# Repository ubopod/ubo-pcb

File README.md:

# Ubo PCBs

Open hardware design files for the printed circuit boards in the [Ubo Pod](https://getubo.com)
and its accessories — the main Raspberry Pi HAT, the side connector board, PCIe and M.2
adapters, a flex cable, and an NFC board. Sources are a mix of **Eagle CAD** and **KiCad**;
newer designs are KiCad.

<table>
  <tr>
    <td align="center" width="33%">
      <br>
      <sub><b><a href="boards/ubo-sideboard/">Sideboard</a></b><br>ports to the back panel</sub>
    </td>
    <td align="center" width="33%">
      <br>
      <sub><b><a href="boards/ubo-hab-v2/">HAB v2</a></b><br>PCIe, USB-C PD and PoE+</sub>
    </td>
    <td align="center" width="33%">
      <br>
      <sub><b><a href="boards/ubo-pcie-adapter/">PCIe adapter</a></b><br>M.2 M-key for the Pi 5</sub>
    </td>
  </tr>
  <tr>
    <td align="center">
      <br>
      <sub><b><a href="boards/m2-mkey-to-aekey/">M.2 M-key to A/E-key</a></b><br>runs a Google Coral</sub>
    </td>
    <td align="center">
      <br>
      <sub><b><a href="boards/pcie-fpc-s-shaped/">S-shaped PCIe FPC</a></b><br>2-layer flex cable</sub>
    </td>
    <td align="center">
      <br>
      <sub><b>As fabricated</b><br>a populated sideboard</sub>
    </td>
  </tr>
</table>

## Boards

Each board lives in its own directory under [`boards/`](boards/) with its own README.

| Board | Rev | Tool | Status | Connects to |
|---|---|---|---|---|
| [**ubo-top-hat**](boards/ubo-top-hat/) | v1.6 | Eagle | Production | Raspberry Pi 40-pin header |
| [**ubo-sideboard**](boards/ubo-sideboard/) | v1.5.2 | KiCad | Current | Pi 4/5 side ports + top HAT |
| ↳ [v1.4](boards/ubo-sideboard/v1.4-eagle/) | v1.4 | Eagle | Superseded by v1.5.2 | — |
| [**ubo-hab-v2**](boards/ubo-hab-v2/) | v4 | KiCad | Current | Raspberry Pi 5 PCIe + power |
| [**ubo-pcie-adapter**](boards/ubo-pcie-adapter/) | v3 | KiCad | Superseded by HAB v2 | Raspberry Pi 5 PCIe |
| [**m2-mkey-to-aekey**](boards/m2-mkey-to-aekey/) | — | KiCad | Built and tested | M.2 M-key slot |
| [**pcie-fpc-s-shaped**](boards/pcie-fpc-s-shaped/) | v2 | KiCad | Prototype, revision in progress | PCIe adapter FPC connectors |
| [**ubo-nfc-hat**](boards/ubo-nfc-hat/) | 1.0 | KiCad | Experimental | I²C via 1×8 headers |

**What each one is:**

- **ubo-top-hat** — the main Ubo board. LCD, keypad, RGB LED ring, WM8960 audio with speakers and
  microphones, IR transmit/receive, temperature and light sensors, EEPROM, fan, power button, and
  an experimental SDR section.
- **ubo-sideboard** — brings the Pi's mini HDMI, USB-C power, and audio jack around to the back of
  the enclosure, and adds a microSD extender, STEMMA Qt connectors, a power button, and a fan header.
- **ubo-hab-v2** — "hardware added on the bottom." PCIe to M.2 M-key, with optional USB-C PD and
  PoE+ power input modules and 12V/5V/3.3V breakouts.
- **ubo-pcie-adapter** — the first HAB revision; a simpler PCIe to M.2 M-key adapter.
- **m2-mkey-to-aekey** — adapts an M.2 M-key slot to A/E-key, so a Google Coral accelerator can go
  where an NVMe drive would.
- **pcie-fpc-s-shaped** — a 2-layer S-shaped FPC cable matching the connector positions on the
  PCIe adapter.
- **ubo-nfc-hat** — NTAG I²C plus NFC tag with a chain of addressable RGB LEDs.

## Repository layout

One directory per board. Within a board directory:

```
boards/<board>/
  README.md          documentation for this board
  <design files>     KiCad project or Eagle .sch/.brd at the top level,
                     or in a <rev>-<tool>/ subdirectory when a board has
                     more than one revision (see ubo-sideboard)
  images/            renders, layout screenshots, photos
  docs/              exported schematic and assembly PDFs
  datasheets/        datasheets for the components used on this board
  mechanical/        board outline DXF, STEP and other 3D models
```

Not every board has every subdirectory — they exist where there is something to put in them.

## Opening the files

- **KiCad projects** (`.kicad_pro`) — KiCad 8 or 9. Open the `.kicad_pro`, not the individual
  schematic or board files, so the project's library tables load.
- **Eagle designs** (`.sch` / `.brd`) — authored in Eagle CAD 9.6.2. KiCad can also import them
  via *File → Import → Non-KiCad Project*.

## License

Copyright © Ubo Pod.

These designs are licensed under the **CERN Open Hardware Licence Version 2 – Strongly
Reciprocal** (`CERN-OHL-S-2.0`). The full text is in [LICENSE](LICENSE).

In plain terms:

- **You can** use, study, modify, manufacture, and sell these boards, commercially or not.
- **If you distribute a modified design**, you have to release your modified source under this
  same licence, so the next person gets what you got.
- **If you sell or give away a product** made from these designs, you have to tell the recipient
  where to obtain the source for it.
- **There is no warranty.** These are hobbyist and small-batch designs; verify them yourself
  before committing to a fabrication run.

That summary is for orientation only — [LICENSE](LICENSE) is the document that actually governs.

To reuse a board here, keep the copyright and licence notices in the design files, and note your
own changes.

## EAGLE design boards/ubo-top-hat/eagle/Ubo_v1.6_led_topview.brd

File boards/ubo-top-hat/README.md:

# Ubo Top HAT (Top PCB)

The main Ubo board — a Raspberry Pi HAT carrying the display, keypad, LED ring, audio, sensors, and IR.
Designed in Eagle CAD 9.6.2. See the [repository index](../../README.md) for the other boards.

| | |
|---|---|
| **Revision** | v1.6 (Eagle source) / v1.6.1 (exported schematic PDF) |
| **Tool** | Eagle CAD 9.6.2 |
| **Interface** | Raspberry Pi 40-pin header |

## Files

| Path | Contents |
|---|---|
| [`eagle/`](eagle/) | Eagle schematic and board layout (`Ubo_v1.6_led_topview.sch` / `.brd`) |
| [`docs/`](docs/) | [Full SKU schematic PDF (v1.6.1)](docs/Ubo_v1.6.1_schematic_full_SKU.pdf) |
| [`datasheets/`](datasheets/) | Datasheets for the components used below |
| [`images/`](images/) | Schematic excerpts for each sub-system |
| [`mechanical/`](mechanical/) | Board outline DXF and 3D model archive |

## Top PCB Overview

In designing Ubo Top PCB (HAT), we tried to use popular components that have already gained adoption among the developer community and are developer friendly. In addition, we made sure that we can source these components for manufacturing. There are several development boards with one or several of these components that you can buy from either Sparkfun, Adafruit, Tindie, SeedStudio or other vendors. At the end of this repo, we have provided links to some of the development boards as reference.

The main objective in designing Ubo was centred around improving developer and end-user experience through offering a rich user interface. Since Raspberry Pi by itself is just a compute brain with no peripherals, it is often challenging to offer a compelling UX/UI to the end user without an interface.

In the following section, we discuss how each sub-system was chosen to enhance user and developer experience as well as technical details of implementation.

## RASPBERRY PI HEADER

## LCD

backlight is connected to GPIO26
TODO: link to datasheet

## Keypad

You can access the datasheet for GPIO Expander [here](datasheets/AW9523_GPIO_expander.pdf)

## RGB LED Ring

## Audio
### Speakers
### Line Out
### Microphones

## Temperature sensor

## Light Sensor

## EEPROM

## Fan

## Power Button

## Security

## Experimental SDR

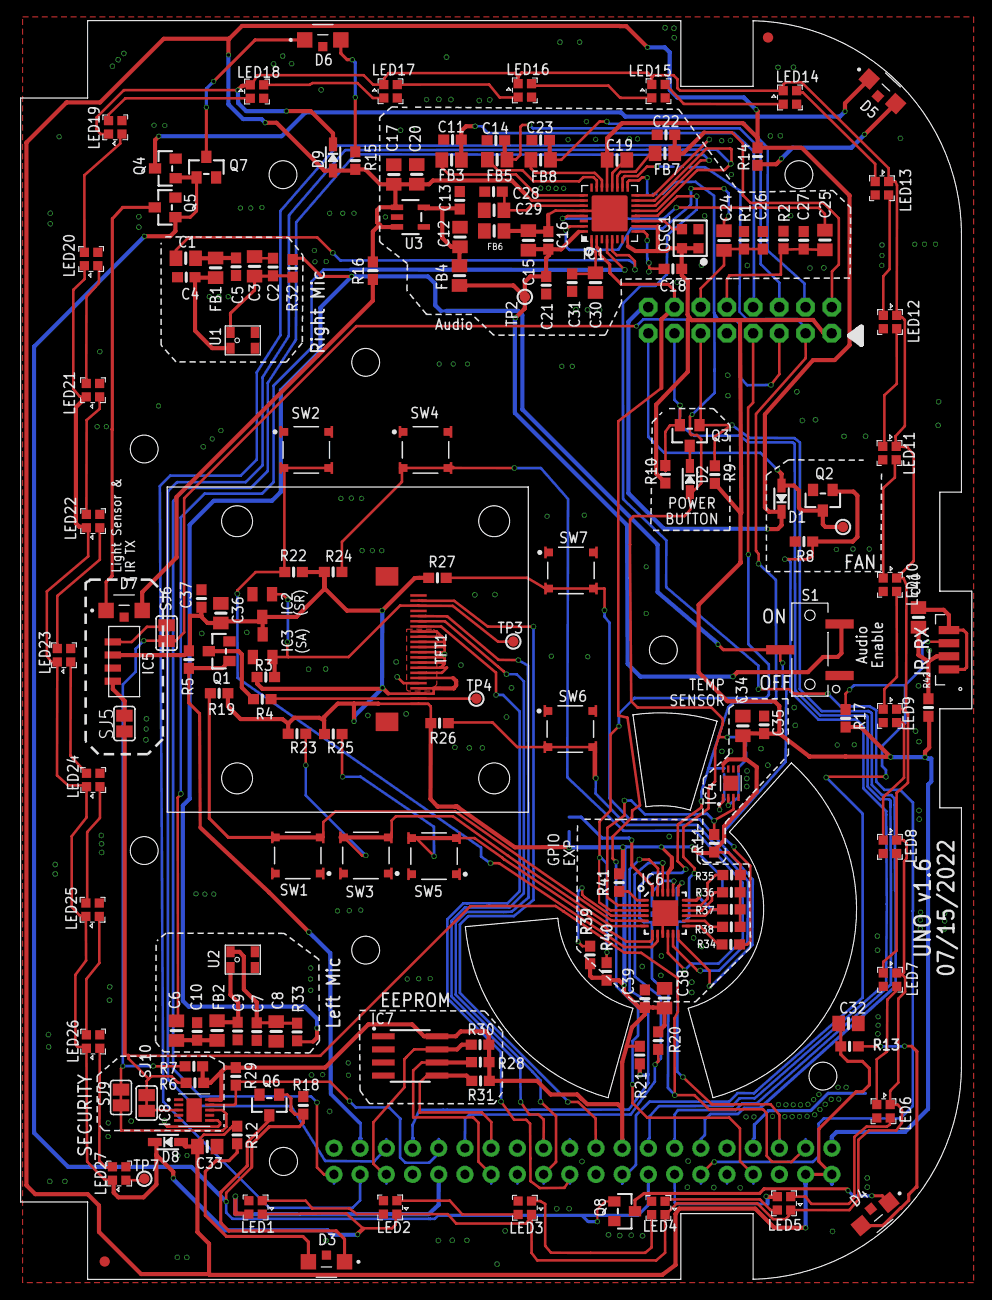
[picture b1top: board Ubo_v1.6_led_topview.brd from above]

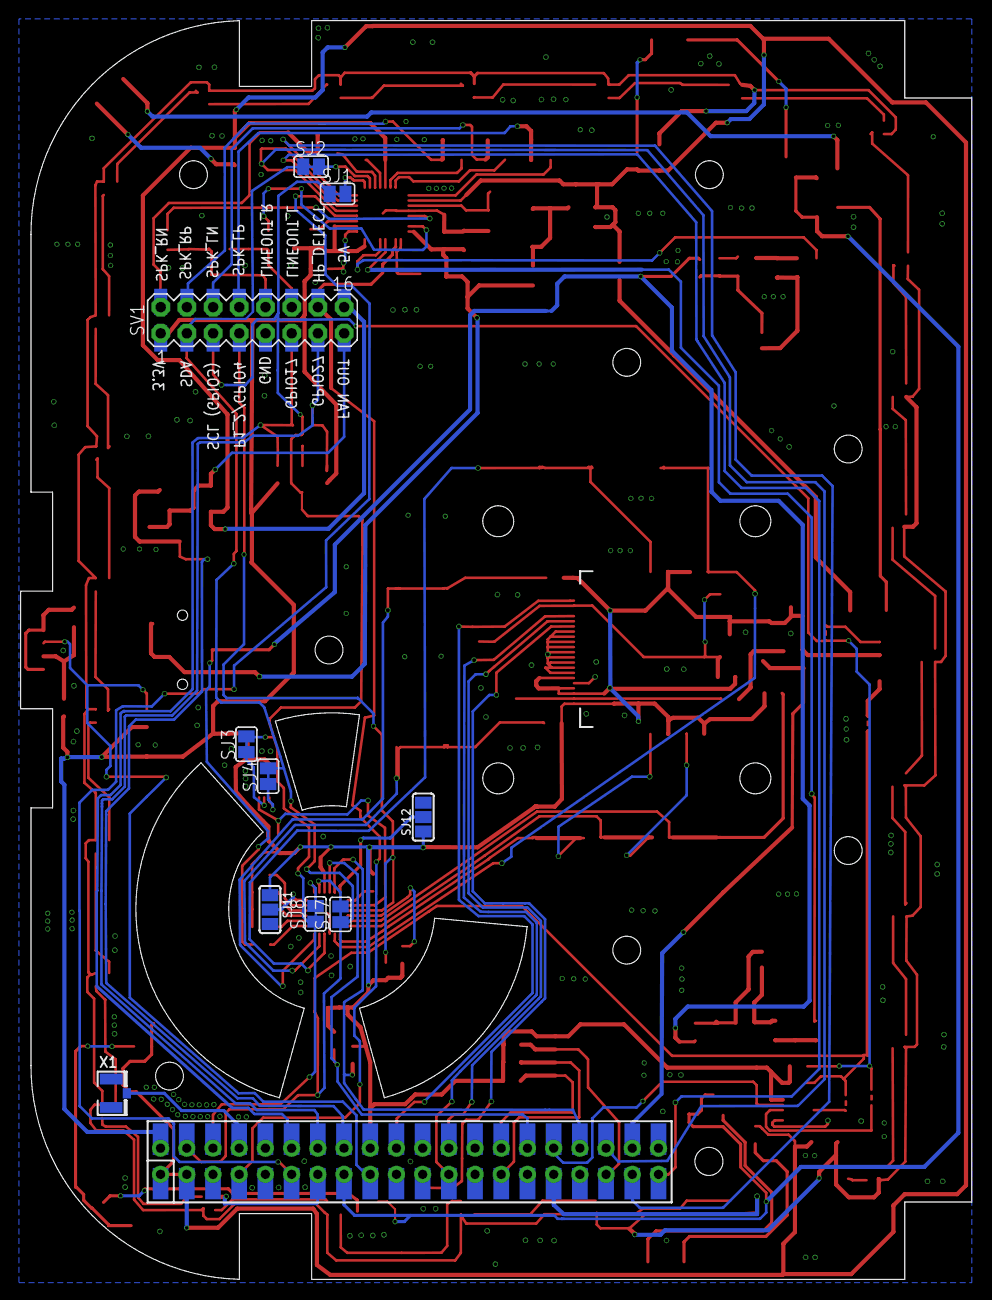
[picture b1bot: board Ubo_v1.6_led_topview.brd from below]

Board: 2 copper layers, 92.2 x 122.0 mm, 178 parts (10 on the bottom side), 130 nets.

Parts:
C1, C3, C6, C8, C12, C15, C17, C19, C20, C29, C30, C32, C33, C34, C36, C38, C40: 10uF; 0805-NO
C2, C7, C13, C16, C18, C21, C28, C31, C35, C37, C39: 0.1uF; 0603-NO
C4, C5, C9, C10: 33pF; 0603-NO
C11, C14, C22, C23, C26, C27: 100pF; 0603-NO
C24, C25: 47uF; 0805-NO
D1, D2, D8, D9: 1N4148; SOD-323
D3, D4, D5, D6, D7: VSMB10940; DIO_VSMB10940
FB1, FB2, FB3, FB4, FB5, FB6, FB7, FB8: Ferrite; 0805-NO
FID1, FID2: FIDUCIAL_1MM
IC1: WM8960; QFN32_5MM
IC2, IC3: APX803-SAG; SOT23
IC4: PCT2075D8-HWSON; SON127P600X800X80-9N
IC5: VEML7700
IC6: AW9523; QFN24_4MM_SMSC
IC7: CAT24C32WI-GT3; SOIC127P600X175-8N
IC8: SLS32AIA020X2USON10XTMA4; SON50P300X300X60-11N
IR1: TSMP77000
LED1, LED2, LED3, LED4, LED5, LED6, LED7, LED8, LED9, LED10, LED11, LED12, LED13, LED14, LED15, LED16, LED17, LED18, LED19, LED20, LED21, LED22, LED23, LED24, LED25, LED26, LED27: LC8812B-3210; SK6805-EC15
OSC1: ECS-3225MV; OSC_2.5X2MM
Q1, Q2, Q3, Q4, Q5, Q6, Q7, Q8: BSS138; SOT23-WIDE
R1, R2, R3, R5, R6, R7, R8, R9, R10, R11, R17, R18, R19, R20, R21, R22, R23, R24, R25, R26, R27, R29, R30, R34, R35, R36, R37, R38, R39, R40, R41: 10K; 0603-NO
R4, R12, R13, R14, R15, R16, R32, R33, R42: 20; 0603-NO
R28, R31: 3.9K; 0603-NO
RPI1: RASPBERRYPI_BPLUS_PIN_2X20_SMTTHM; PI_PIN_2X20_SMTTHM
S1: JS102011JCQNMS-12D17E; SW_MS-12D17E
SJ1, SJ2, SJ3, SJ4, SJ5, SJ6, SJ7, SJ8, SJ9, SJ10: SJ
SJ11, SJ12: SOLDERJUMPER_2WAY_OPEN_NOPASTE
SV1: MA08-2
SW1, SW2, SW3, SW4, SW5, SW6, SW7: E-SWITCH_TL3315NF160Q_0
TFT1: DISP_TFT_1.54IN_240X240_22P_TOP_FPC; TFT_1.54IN_240X240_22PN_TOP_FPC
TP2, TP3, TP4, TP6, TP7: TESTPOINT_ROUND_1MM
U1, U2: MIC; SPW2430HR5H-B
U3: AP2112-3.3K; SOT23-5
X1: U.FL

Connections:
3.3V: C18.1, C34.1, C35.1, C36.1, C37.1, C38.1, C39.1, IC1.8, IC1.10, IC2.3, IC3.3, IC4.P$8, IC5.2, IC6.21, IC7.8, IC8.10, OSC1.1, OSC1.4, R3.2, R5.2, R6.1, R7.1, R9.1, R10.1, R11.1, R17.1, R19.1, R20.1, R21.1, R22.1, R23.1, R24.1, R25.1, R26.1, R27.1, R28.1, R29.1, R30.1, R31.1, R35.1, R36.1, R37.1, R38.1, R39.1, R40.1, R41.1, R42.1, RPI1.1, RPI1.17, RPI1.S1, RPI1.S17, SJ11.1, SJ12.1, SV1.1, SV1.P$1, TFT1.1, TFT1.3, TFT1.4, TFT1.6
5.0V: C17.1, C19.1, C20.1, C32.1, C33.1, D1.C, D8.A, D9.A, IC1.21, IC1.26, R12.1, R13.1, R14.1, R15.1, R16.1, RPI1.2, RPI1.4, RPI1.S2, RPI1.S4, SV1.16, SV1.P$16, U3.1, U3.3
AGND: C15.2, C16.2, FB6.1, IC1.28, IC1.33
AVDD: C15.1, C16.1, C21.1, FB4.1, IC1.32, S1.3, TP2.P$1
AVDD_EN: R32.2, R33.2, R34.2, S1.2
BUTTON_E_DOWN: IC6.10, R24.2, SW4.3, SW4.3-2, SW4.4, SW4.4-2
BUTTON_E_UP: IC6.8, R22.2, SW2.3, SW2.3-2, SW2.4, SW2.4-2
BUTTON_S_LEFT: IC6.11, R26.2, SW6.3, SW6.3-2, SW6.4, SW6.4-2
BUTTON_S_RIGHT: IC6.12, R27.2, SW7.3, SW7.3-2, SW7.4, SW7.4-2
BUTTON_W_DOWN: IC6.7, R25.2, SW5.3, SW5.3-2, SW5.4, SW5.4-2
BUTTON_W_MIDDLE: IC6.6, R23.2, SW3.3, SW3.3-2, SW3.4, SW3.4-2
BUTTON_W_UP: IC6.5, R19.2, SW1.3, SW1.3-2, SW1.4, SW1.4-2
EECLK: IC7.6, R28.2, RPI1.28, RPI1.S28
EEDATA: IC7.5, R31.2, RPI1.27, RPI1.S27
EEPROM_WP: IC7.7, R30.2, RPI1.36, RPI1.S36
FAN_IN: Q2.1, R8.1, RPI1.15, RPI1.S15
FAN_OUT: D1.A, Q2.3, SV1.15, SV1.P$15, TP6.P$1
GND: C2.2, C3.2, C4.2, C5.2, C7.2, C8.2, C9.2, C10.2, C11.2, C12.2, C13.2, C14.2, C17.2, C18.2, C19.2, C20.2, C21.2, C22.2, C23.2, C26.2, C27.2, C28.2, C29.2, C30.2, C31.2, C32.2, C33.2, C34.2, C35.2, C36.2, C37.2, C38.2, C39.2, C40.2, FB6.2, IC1.9, IC1.20, IC1.24, IC2.2, IC3.1, IC4.P$4, IC4.P$5, IC4.P$6, IC4.P$7, IC4.P$9, IC5.3, IC6.9, IC6.THERM, IC7.1, IC7.2, IC7.3, IC7.4, IC8.1, IC8.2, IC8.4, IC8.5, IC8.6, IC8.7, IC8.11, IR1.P$1, IR1.P$4, LED1.P$4, LED2.P$4, LED3.P$4, LED4.P$4, LED5.P$4, LED6.P$4, LED7.P$4, LED8.P$4, LED9.P$4, LED10.P$4, LED11.P$4, LED12.P$4, LED13.P$4, LED14.P$4, LED15.P$4, LED16.P$4, LED17.P$4, LED18.P$4, LED19.P$4, LED20.P$4, LED21.P$4, LED22.P$4, LED23.P$4, LED24.P$4, LED25.P$4, LED26.P$4, LED27.P$4, OSC1.2, Q1.2, Q2.2, Q4.2, Q5.2, Q6.2, Q7.2, Q8.2, R1.1, R2.1, R8.2, R18.2, RPI1.6, RPI1.9, RPI1.14, RPI1.20, RPI1.25, RPI1.30, RPI1.34, RPI1.39, RPI1.S6, RPI1.S9, RPI1.S14, RPI1.S20, RPI1.S25, RPI1.S30, RPI1.S34, RPI1.S39, S1.1, SJ11.3, SJ12.3, SV1.9, SV1.P$9, SW1.1, SW1.1-2, SW1.2, SW1.2-2, SW2.1, SW2.1-2, SW2.2, SW2.2-2, SW3.1, SW3.1-2, SW3.2, SW3.2-2, SW4.1, SW4.1-2, SW4.2, SW4.2-2, SW5.1, SW5.1-2, SW5.2, SW5.2-2, SW6.1, SW6.1-2, SW6.2, SW6.2-2, SW7.1, SW7.1-2, SW7.2, SW7.2-2, TFT1.5, TFT1.7, TFT1.8, TFT1.9, TFT1.10, TFT1.11, TFT1.12, TFT1.13, TFT1.14, TFT1.15, TFT1.22, TFT1.SUPPORT1, TFT1.SUPPORT2, U1.2, U1.3, U2.2, U2.3, U3.2, X1.1, X1.2
GPIO4: RPI1.7, RPI1.S7, X1.3
GPIO17: Q3.1, R9.2, RPI1.11, RPI1.S11, SV1.11, SV1.P$11
GPIO27: Q3.2, R10.2, RPI1.13, RPI1.S13, SV1.13, SV1.P$13
GPIO_15: RPI1.10, RPI1.S10
GPIO_EXP_RST: IC6.23, R21.2, RPI1.33, RPI1.S33
HEADPHONE_DETECT: IC1.2, RPI1.8, RPI1.S8, SV1.14, SV1.P$14
I2S_BCLK: IC1.12, RPI1.12, RPI1.S12
I2S_DIN: IC1.16, RPI1.38, RPI1.S38
I2S_DOUT: IC1.14, RPI1.40, RPI1.S40
I2S_LRCLK: IC1.13, IC1.15, RPI1.35, RPI1.S35
INT: IC6.22, R20.2, RPI1.29, RPI1.S29
IR_RX: IR1.P$3, R17.2, RPI1.18, RPI1.S18
IR_TX: Q4.1, Q5.1, Q6.1, Q7.1, Q8.1, R18.1, RPI1.16, RPI1.S16
LEDK: R4.2, TFT1.2, TP4.P$1
LED_POWER: D8.C, D9.C, LED1.P$2, LED2.P$2, LED3.P$2, LED4.P$2, LED5.P$2, LED6.P$2, LED7.P$2, LED8.P$2, LED9.P$2, LED10.P$2, LED11.P$2, LED12.P$2, LED13.P$2, LED14.P$2, LED15.P$2, LED16.P$2, LED17.P$2, LED18.P$2, LED19.P$2, LED20.P$2, LED21.P$2, LED22.P$2, LED23.P$2, LED24.P$2, LED25.P$2, LED26.P$2, LED27.P$2
LED_PWM0: LED1.P$1, RPI1.32, RPI1.S32
LINEOUT_LEFT: C24.2, C26.1, R1.2, SV1.12, SV1.P$12
LINEOUT_RIGHT: C25.2, C27.1, R2.2, SV1.10, SV1.P$10
LINPUT1: C6.2, IC1.4
LITE: Q1.1, R5.1, RPI1.37, RPI1.S37
MCLK: IC1.11, OSC1.3
MICBIAS: C30.1, C31.1, IC1.1
unnamed: FB7.1, IC1.19
unnamed: FB8.1, IC1.22
unnamed: LED27.P$3, TP7.P$1
unnamed: Q1.3, R4.1
unnamed: IC6.20, SJ7.2
unnamed: D7.A, R16.2
unnamed: D3.C, Q6.3
unnamed: D2.C, Q3.3
unnamed: IC6.19, SJ8.2
unnamed: IC6.4, R39.2
unnamed: IC6.14, R38.2
unnamed: C4.1, FB1.1, U1.1
unnamed: C9.1, FB2.1, U2.1
unnamed: LED1.P$3, LED2.P$1
unnamed: LED2.P$3, LED3.P$1
unnamed: C1.1, C5.1, FB1.2
unnamed: C6.1, C10.1, FB2.2
unnamed: LED3.P$3, LED4.P$1
unnamed: IC6.15, R37.2
unnamed: LED4.P$3, LED5.P$1
unnamed: FB3.1, IC1.25
unnamed: FB5.1, IC1.23
unnamed: LED6.P$3, LED7.P$1
unnamed: LED7.P$3, LED8.P$1
unnamed: LED9.P$3, LED10.P$1
unnamed: LED10.P$3, LED11.P$1
unnamed: LED14.P$3, LED15.P$1
unnamed: LED15.P$3, LED16.P$1
unnamed: LED16.P$3, LED17.P$1
unnamed: LED17.P$3, LED18.P$1
unnamed: LED20.P$3, LED21.P$1
unnamed: LED21.P$3, LED22.P$1
unnamed: LED22.P$3, LED23.P$1
unnamed: LED23.P$3, LED24.P$1
unnamed: LED5.P$3, LED6.P$1
unnamed: LED13.P$3, LED14.P$1
unnamed: LED19.P$3, LED20.P$1
unnamed: IC6.16, R36.2
unnamed: LED11.P$3, LED12.P$1
unnamed: LED12.P$3, LED13.P$1
unnamed: LED24.P$3, LED25.P$1
unnamed: LED25.P$3, LED26.P$1
unnamed: C24.1, IC1.31
unnamed: C25.1, IC1.29
unnamed: IC6.17, R35.2
unnamed: IC1.17, SJ1.2
unnamed: IC1.18, SJ2.2
unnamed: IC5.4, SJ5.2
unnamed: IC5.1, SJ6.2
unnamed: IC4.P$2, SJ3.1
unnamed: IC4.P$1, SJ4.1
unnamed: IC8.8, SJ9.2
unnamed: IC8.3, SJ10.2
unnamed: D6.A, R15.2
unnamed: D5.A, R14.2
unnamed: D4.A, R13.2
unnamed: D3.A, R12.2
unnamed: LED8.P$3, LED9.P$1
unnamed: LED18.P$3, LED19.P$1
unnamed: LED26.P$3, LED27.P$1
unnamed: C7.1, C8.1, R33.1, U2.4
unnamed: C2.1, C3.1, R32.1, U1.4
unnamed: IC6.13, R34.1
unnamed: IC6.24, SJ12.2
unnamed: IC6.18, SJ11.2
unnamed: D5.C, Q4.3
unnamed: D4.C, Q8.3
unnamed: D6.C, Q7.3
unnamed: D7.C, Q5.3
unnamed: C40.1, IR1.P$2, R42.2
OUT: C12.1, C13.1, FB4.2, U3.5
P1_0: IC6.1, R41.2
P1_2: IC6.3, R40.2, SV1.7, SV1.P$7
RINPUT1: C1.2, IC1.5
SCL: D2.A, R7.2, RPI1.5, RPI1.S5, SJ1.1, SJ3.2, SJ6.1, SJ8.1, SJ9.1, SV1.5, SV1.P$5
SDA: R6.2, RPI1.3, RPI1.S3, SJ2.1, SJ4.2, SJ5.1, SJ7.1, SJ10.1, SV1.3, SV1.P$3
SECURITY_RESET: IC8.9, R29.2, RPI1.31, RPI1.S31
SPI_CE1: RPI1.26, RPI1.S26
SPI_MISO: RPI1.21, RPI1.S21
SPK_LN: C14.1, FB5.2, SV1.6, SV1.P$6
SPK_LP: C11.1, FB3.2, SV1.8, SV1.P$8
SPK_RN: C22.1, FB7.2, SV1.2, SV1.P$2
SPK_RP: C23.1, FB8.2, SV1.4, SV1.P$4
TEMP_INT: IC4.P$3, IC6.2, R11.2
TFT_CS: RPI1.24, RPI1.S24, TFT1.18
TFT_DC: RPI1.22, RPI1.S22, TFT1.16
TFT_MOSI: RPI1.19, RPI1.S19, TFT1.21
TFT_RESET: IC2.1, IC3.2, R3.1, TFT1.20, TP3.P$1
TFT_SCLK: RPI1.23, RPI1.S23, TFT1.17
VMID: C28.1, C29.1, IC1.27

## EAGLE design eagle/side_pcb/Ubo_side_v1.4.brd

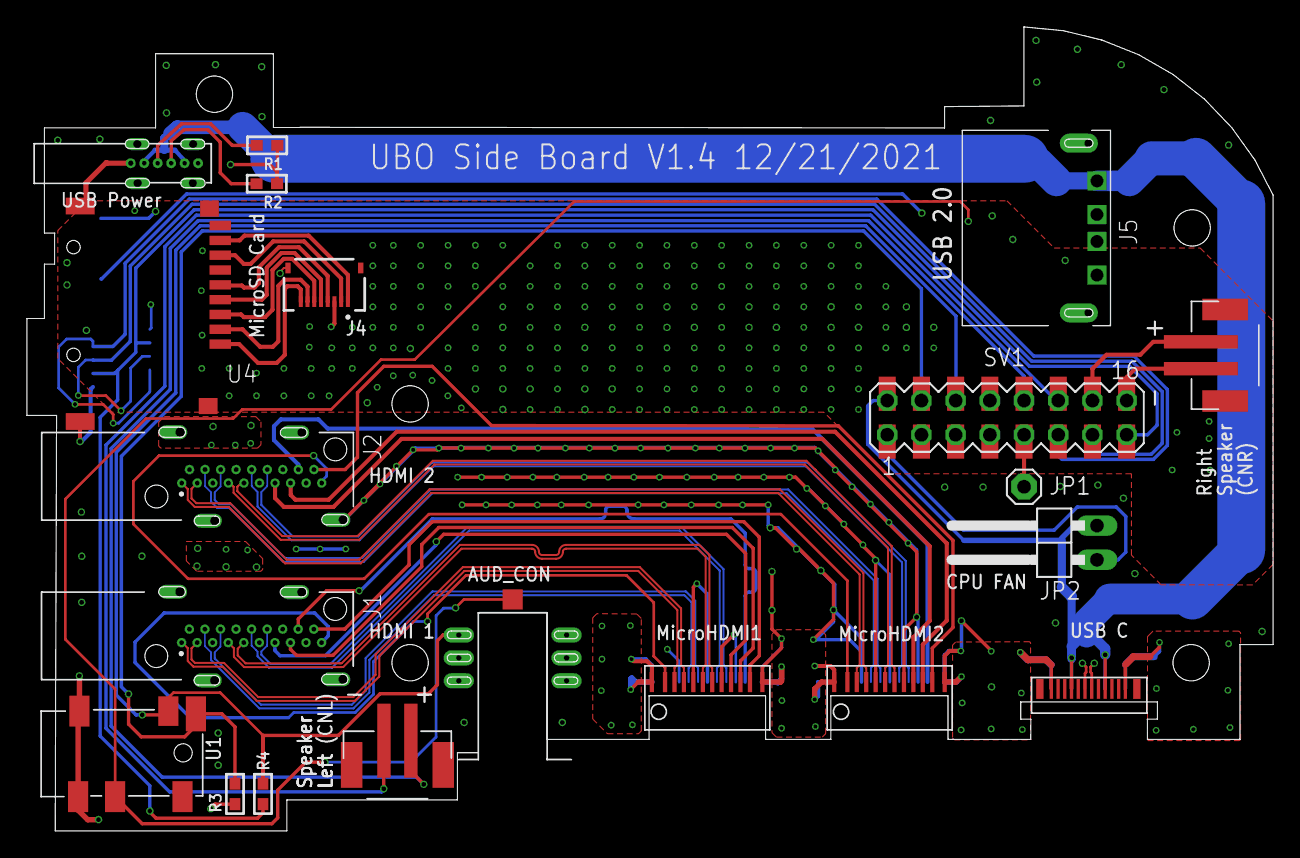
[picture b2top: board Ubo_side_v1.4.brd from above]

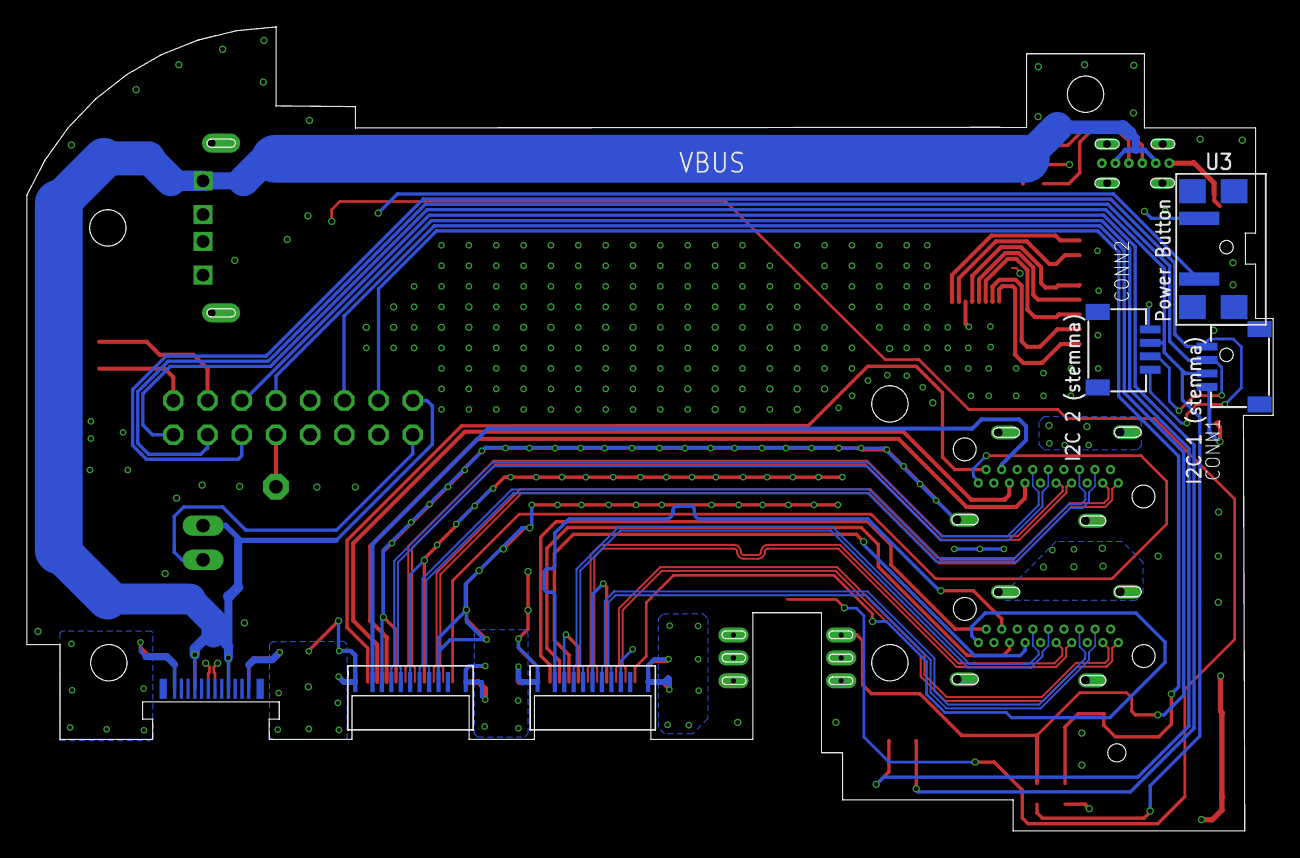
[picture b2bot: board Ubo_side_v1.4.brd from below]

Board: 4 copper layers, 92.5 x 59.7 mm, 23 parts (5 on the bottom side), 53 nets.

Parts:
AUD_CON: AUDIO_3.5MMJACK_MALE; AUDIO_3.5MM_JACK_MALE
CN_SPK_L: JST-PH-2-SMT
CN_SPK_R: JST-PH-2-SMT
CONN1, CONN2: STEMMA_I2C_QT; JST_SH4
J1, J2: HDMI-KDMIX-SL1-NS-WS-B15; CONN_KDMIX-SL1-NS-WS-B15
J4: FFC2B28-08-G; GCT_FFC2B28-08-G
J5: USB-A-S-X-X-SM2RA03B-DT98; USB-A-RA03B-DT98
JP1: 1X01
JP2: 1X02/90
MICROHDMI1, MICROHDMI2: MICRO_HDMI_JTHDDM
R1: 5.1k; _0603
R2: 5.1K; _0603
R3: 100K; _0603
R4: 1K; _0603
SV1: MA08X2-FEMALE
U1: AUDIO_SOCKET_JHP_328BPJ-3160; PJ-3160
U2: USB-20C-F-06CD-1; USB_20C_F_60CD
U3: TS06105SA; TS-06105SA-1
U4: MICROSDTF01-H1.8; MICROSDTF-01-H1.8
USBC: USB_TYPE_MALE_31C_J10C; USB_TYPE_MALE_31C_J10A

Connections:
3.3V: CONN1.2, CONN2.2, R4.2, SV1.15, SV1.P$15
5V_A: J1.18, MICROHDMI1.19
5V_B: J2.18, MICROHDMI2.19
A5: R1.2, U2.A5
B5: R2.2, U2.B5
CEC_A: J1.13, MICROHDMI1.15
CEC_B: J2.13, MICROHDMI2.15
CLK_SD: J4.4, U4.P$5
CMD_SD: J4.6, U4.P$3
DAT0: J4.2, U4.P$7
DAT1: J4.1, U4.P$8
DAT2: J4.8, U4.P$1
DAT3: J4.7, U4.P$2
DDC_CLOCK_A: J1.15, MICROHDMI1.17
DDC_CLOCK_B: J2.15, MICROHDMI2.17
DDC_DATA_A: J1.16, MICROHDMI1.18
DDC_DATA_B: J2.16, MICROHDMI2.18
D_N: J5.P$2, USBC.A6
D_P: J5.P$3, USBC.A7
FAN_OUT: JP2.1, SV1.1, SV1.P$1
GND: AUD_CON.P$1L, AUD_CON.P$1R, AUD_CON.P$2L, AUD_CON.P$2R, CONN1.1, CONN2.1, J1.2, J1.5, J1.8, J1.11, J1.17, J1.S1, J1.S2, J1.S3, J1.S4, J2.2, J2.5, J2.8, J2.11, J2.17, J2.S1, J2.S2, J2.S3, J2.S4, J4.3, J4.S1, J4.S2, J5.P$4, J5.SH$1, J5.SH$2, MICROHDMI1.4, MICROHDMI1.7, MICROHDMI1.10, MICROHDMI1.13, MICROHDMI1.16, MICROHDMI1.S1, MICROHDMI1.S2, MICROHDMI1.S3, MICROHDMI1.S4, MICROHDMI2.4, MICROHDMI2.7, MICROHDMI2.10, MICROHDMI2.13, MICROHDMI2.16, MICROHDMI2.S1, MICROHDMI2.S2, MICROHDMI2.S3, MICROHDMI2.S4, R1.1, R2.1, R3.1, SV1.7, SV1.P$7, U1.1, U1.2, U2.A12, U2.B12, U3.A, U4.GND$1, U4.GND$2, U4.GND$3, U4.GND$4, U4.P$6, USBC.A1, USBC.A12, USBC.B1, USBC.B12
GPIO17: SV1.5, SV1.P$5
GPIO27: SV1.3, SV1.P$3, U3.B
HOT_PLUG_A: J1.19, MICROHDMI1.1
HOT_PLUG_B: J2.19, MICROHDMI2.1
HP_DETECT: R3.2, SV1.4, SV1.P$4, U1.6
LINEOUT_L: AUD_CON.P$3L, AUD_CON.P$3R, R4.1, SV1.6, SV1.P$6, U1.4
LINEOUT_R: AUD_CON.P$4, SV1.8, SV1.P$8, U1.3
unnamed: JP1.1, SV1.9, SV1.P$9
SCL: CONN1.4, CONN2.4, SV1.11, SV1.P$11
SDA: CONN1.3, CONN2.3, SV1.13, SV1.P$13
SPK_LN: CN_SPK_L.2, SV1.12, SV1.P$12
SPK_LP: CN_SPK_L.1, SV1.10, SV1.P$10
SPK_RN: CN_SPK_R.2, SV1.16, SV1.P$16
SPK_RP: CN_SPK_R.1, SV1.14, SV1.P$14
TMDS_CLOCK_A_N: J1.12, MICROHDMI1.14
TMDS_CLOCK_A_P: J1.10, MICROHDMI1.12
TMDS_CLOCK_B_N: J2.12, MICROHDMI2.14
TMDS_CLOCK_B_P: J2.10, MICROHDMI2.12
TMDS_D0_A_N: J1.9, MICROHDMI1.11
TMDS_D0_A_P: J1.7, MICROHDMI1.9
TMDS_D0_B_N: J2.9, MICROHDMI2.11
TMDS_D0_B_P: J2.7, MICROHDMI2.9
TMDS_D1_A_N: J1.6, MICROHDMI1.8
TMDS_D1_A_P: J1.4, MICROHDMI1.6
TMDS_D1_B_N: J2.6, MICROHDMI2.8
TMDS_D1_B_P: J2.4, MICROHDMI2.6
TMDS_D2_A_N: J1.3, MICROHDMI1.5
TMDS_D2_A_P: J1.1, MICROHDMI1.3
TMDS_D2_B_N: J2.3, MICROHDMI2.5
TMDS_D2_B_P: J2.1, MICROHDMI2.3
VBUS: J5.P$1, JP2.2, SV1.2, SV1.P$2, U2.A9, U2.B9, USBC.A4, USBC.A9, USBC.B4, USBC.B9
VDD_SD: J4.5, U4.P$4

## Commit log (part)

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2023-02-27 added PCB schematic
    will add layout and other files soon
2023-03-11 added datasheets and images
2023-03-11 added more images
2023-04-07 Top PCB DFX Dimensions
2023-04-07 Top PCB Step file 3D model
2023-04-07 added top PCB schematic and layout design files
2023-04-07 added top pcb design files
2023-04-08 changed filename
2023-04-08 moved schematic files to schematic
2023-04-08 moved files
2025-07-29 adding KiCad design files for sideboard v1.5.2
2025-07-29 added schematic image
2025-07-29 updated 3d image
2025-08-29 added M.2 M-key to A/E-key adapter
2025-08-29 added real images for m-key adapter
2025-08-29 add ubo images with adapter and coral
2025-08-29 Enhance README with images and usage information
    Added images and details about the M.2 M-key to A/E-key adapter and its application in Ubo Pod.
2025-08-29 add design files for PCIe adapter
2025-08-29 add readme
2025-08-29 Update README with PCIe adapter details and images
    Added detailed description and images for the PCIe adapter board.
2025-09-03 Enhance README with Ubo Pod details and images
2025-09-03 Fix image paths in Ubo Pod README
2025-09-03 Update README with design inspiration attribution
2025-09-03 add S-shaped FPC cable design
2025-09-03 Enhance README with link and images for FPC cable
    Added link to the PCIe adapter board repository and included images of the FPC cable.
2026-01-17 add new PCIe HAB v2 design
2026-01-18 Add README for Ubo HAB adapter board
    Added detailed README for Ubo HAB PCIe/USB-C/POE+ adapter board, including features, purchasing information, and power module details.
2026-01-18 add images for ubo hab and modules
2026-01-18 Revise power module links in README
    Updated links for power modules in the README.
2026-04-22 add ubo nfc hat design files
2026-04-22 removed unused directory
